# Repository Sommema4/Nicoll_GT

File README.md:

# Nicoll_GT
Gerdien tube documentation

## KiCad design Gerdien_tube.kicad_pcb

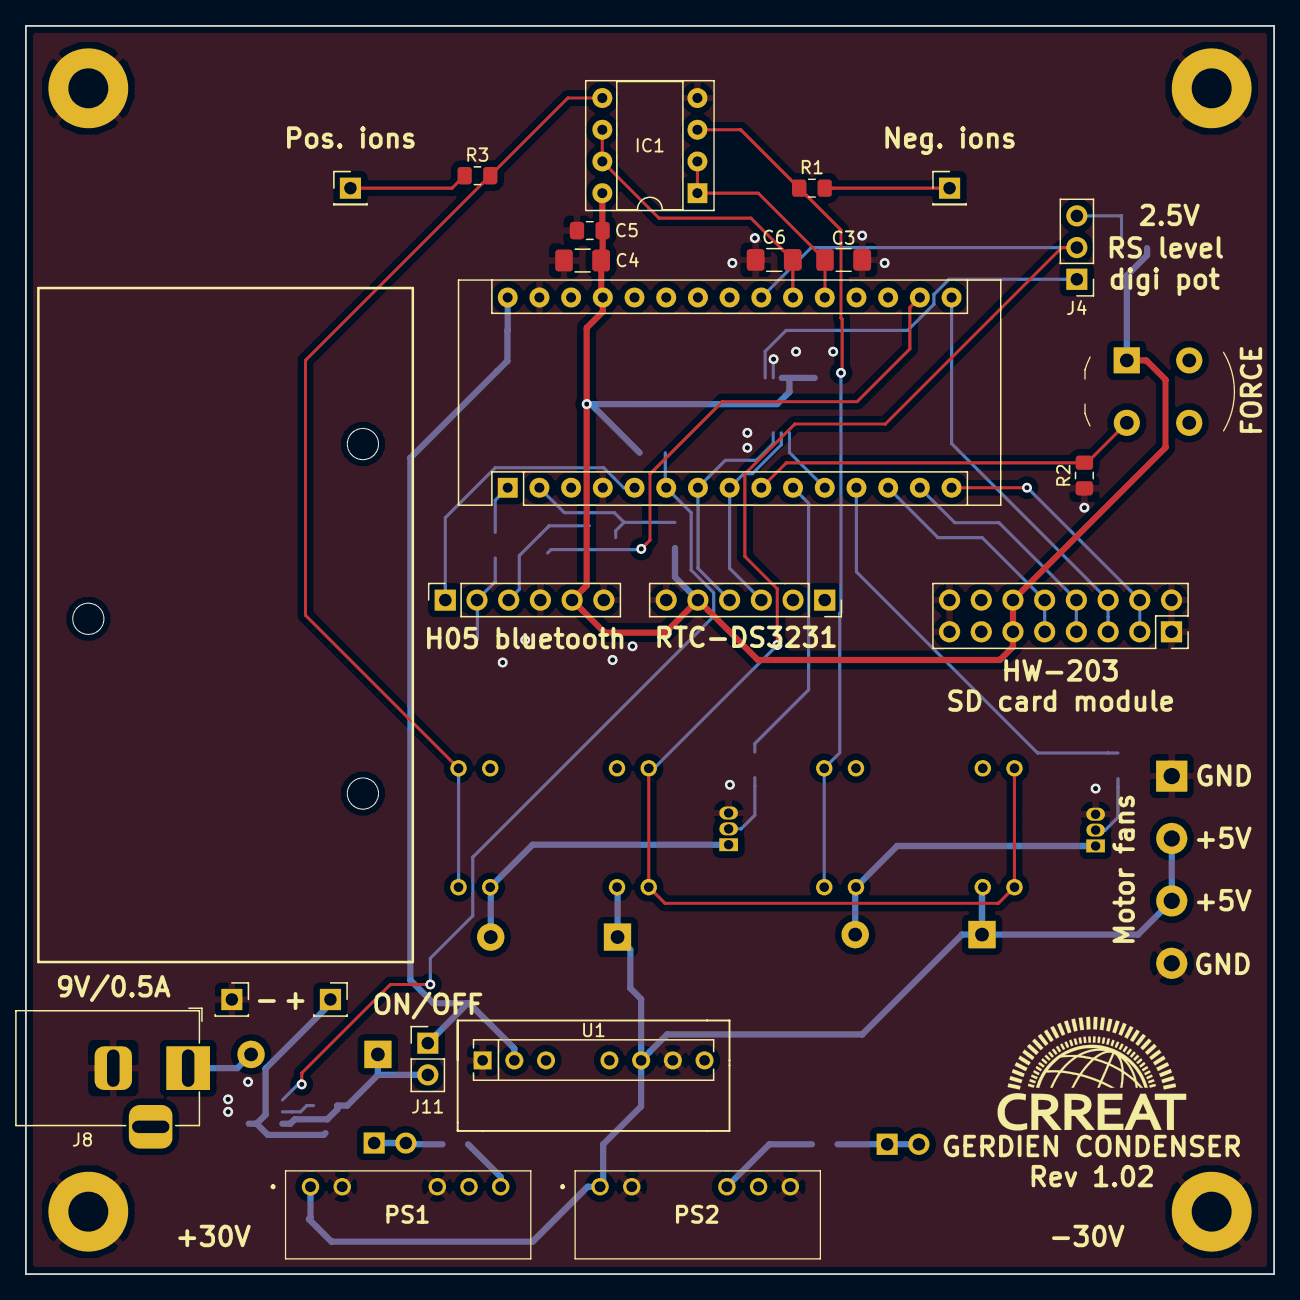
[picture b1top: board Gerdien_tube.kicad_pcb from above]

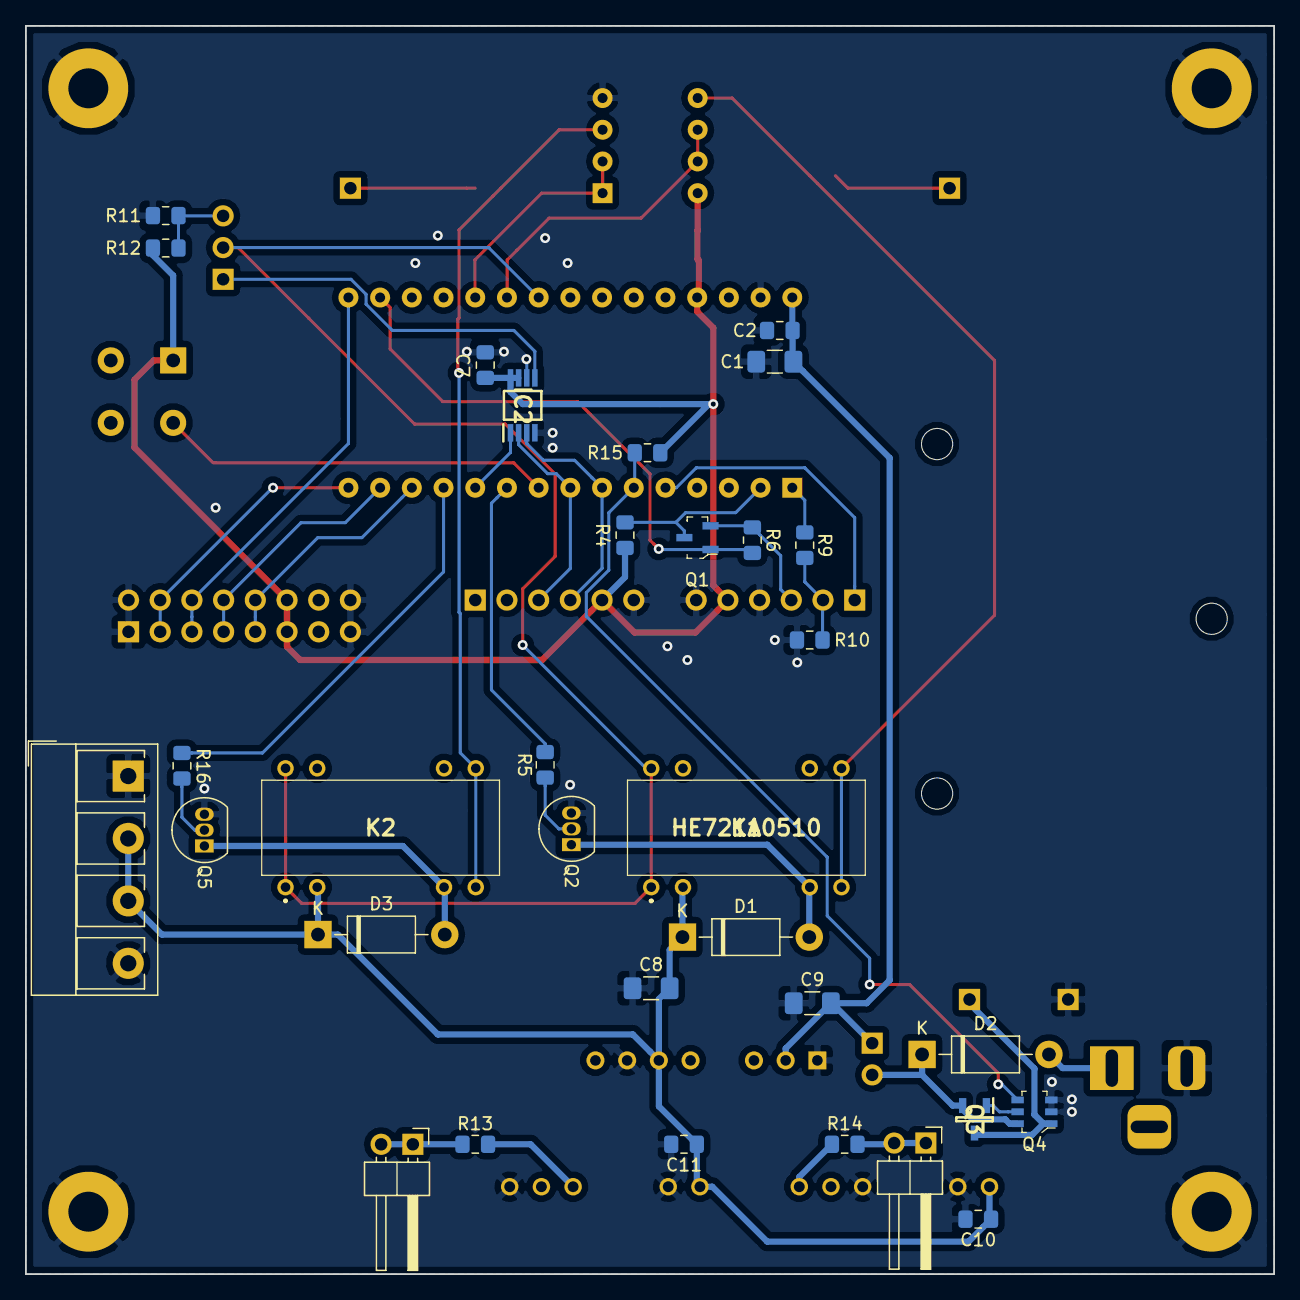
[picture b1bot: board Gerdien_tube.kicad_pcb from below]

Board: 2 copper layers, 100.0 x 100.0 mm, 62 parts (32 on the bottom side), 42 nets.

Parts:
A1: Arduino_Nano_v3.x; Arduino_Nano
C1, C3, C4, C6, C8: 10uF; C_1206_3216Metric_Pad1.42x1.75mm_HandSolder
C2, C7, C10, C11: 1uF; C_0805_2012Metric_Pad1.15x1.40mm_HandSolder
C5: 0.1uF; C_0805_2012Metric_Pad1.15x1.40mm_HandSolder
C9: 22uF; C_1206_3216Metric_Pad1.42x1.75mm_HandSolder
D1, D3: 1N4007; D_DO-41_SOD81_P10.16mm_Horizontal
D2: 1N5819; D_DO-41_SOD81_P10.16mm_Horizontal
IC1: LMC6042IM_NOPB; DIP-8_W7.62mm_Socket
IC2: CAT5140ZI-00-GT3; SOP65P490X110-8N
J1: Conn_02x08_Odd_Even; PinSocket_2x08_P2.54mm_Vertical
J2, J3: Conn_01x06_Female; PinSocket_1x06_P2.54mm_Vertical
J4: Conn_01x03_Male; PinHeader_1x03_P2.54mm_Vertical
J5: Screw_Terminal_01x04; TerminalBlock_RND_205-00278_1x04_P5.00mm_Vertical
J6, J7: Conn_01x01_Female; PinSocket_1x01_P2.54mm_Vertical
J8: Barrel_Jack; BarrelJack_Horizontal
J9, J10: Conn_01x02_Male; PinHeader_1x02_P2.54mm_Horizontal
J11: Conn_01x02_Male; PinHeader_1x02_P2.54mm_Vertical
K1, K2: HE721A0510
MH1, MH2, MH3, MH4: MountingHole_Pad; MountingHole_3.2mm_M3_Pad
MH5, MH6, MH7: MountingHole; MountingHole_2.5mm
PS1, PS2: RH-1215D; RP1212D
Q1: BSS138; SOT-23-3
Q2, Q5: BC547; TO-92_Inline
Q3: FDN306P; SOT95P237X112-3N
Q4: LTC4412ES6_TRMPBF; SOT-23-6
R1, R3: 1M; R_0805_2012Metric_Pad1.15x1.40mm_HandSolder
R2, R4, R6, R13, R14: 10k; R_0805_2012Metric_Pad1.15x1.40mm_HandSolder
R5, R9, R16: 1k; R_0805_2012Metric_Pad1.15x1.40mm_HandSolder
R10: 2k; R_0805_2012Metric_Pad1.15x1.40mm_HandSolder
R11, R12: 5k; R_0805_2012Metric_Pad1.15x1.40mm_HandSolder
R15: 470k; R_0805_2012Metric_Pad1.15x1.40mm_HandSolder
S1: GPTS203211B; PushButton_Round_D12mm_THT_KS-01Q-01
TP1, TP2: TestPoint; PinHeader_1x01_P2.54mm_Vertical
U1: TEC_3-0910; TEC3_0911

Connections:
+3V3: A1.17, Q1.1, R6.2
+5V: A1.27, C4.1, C5.1, C7.2, IC1.8, IC2.7, IC2.8, J1.11, J1.12, J2.5, J3.5, R4.2, R12.1, R15.1, S1.1
+5VP: C8.1, C10.1, C11.1, D1.1, D3.1, J5.2, J5.3, K1.2, K2.2, PS1.1, PS2.1, U1.6
+30V: J9.1, J9.2, R14.2
+BATT: J6.1, Q3.3, Q4.1
+VDC: A1.30, C1.1, C2.1, C9.1, J11.1, U1.2
-30V: J10.1, J10.2, R13.1
BUTTON: A1.9, R2.2, S1.2
CHANNEL_A: A1.20, C3.2, IC1.1, IC1.2
CHANNEL_B: A1.21, C6.2, IC1.6, IC1.7
CHARGE_1: IC1.5, K1.7, K1.8, R3.2
CHARGE_2: IC1.3, K2.7, K2.8, R1.1
CHARGE_LEVEL: A1.22, J4.2, K1.1, K1.14, K2.1, K2.14
CS: A1.13, J1.9, J1.10
DIG_POT: IC2.5, J4.1
GND: A1.4, A1.29, C1.2, C2.2, C3.1, C4.2, C5.2, C6.1, C7.1, C8.2, C9.2, C10.2, C11.2, IC1.4, IC2.4, IC2.6, J1.1, J1.2, J1.15, J1.16, J2.6, J3.4, J3.6, J5.1, J5.4, J7.1, J8.2, MH1.1, MH2.1, MH3.1, MH4.1, PS1.2, PS1.5, PS2.2, PS2.7, Q2.3, Q4.2, Q4.3, Q5.3, R2.1, R10.1, R11.2, U1.1, U1.7
H05_RX: A1.1, R9.2
H05_STATUS: A1.5, J3.1
H05_TX: A1.2, Q1.3, R4.1
MISO: A1.15, J1.3, J1.4
MOSI: A1.14, J1.7, J1.8
unnamed: D1.2, K1.6, Q2.1
unnamed: D2.1, J11.2, Q3.2, Q4.6
unnamed: D2.2, J8.1
unnamed: D3.2, K2.6, Q5.1
unnamed: J3.2, R9.1, R10.2
unnamed: J3.3, Q1.2, R6.1
unnamed: J4.3, R11.1, R12.2
unnamed: PS1.7, R14.1
unnamed: PS2.5, R13.2
unnamed: Q2.2, R5.1
unnamed: Q3.1, Q4.5
unnamed: Q5.2, R16.1
unnamed: R1.2, TP1.1
unnamed: R3.1, TP2.1
PWR_STATUS: A1.6, Q4.4, R15.2
RESET_1: A1.10, R5.2
RESET_2: A1.12, R16.2
SCK: A1.16, J1.5, J1.6
SCL: A1.8, IC2.2, J2.3
SDA: A1.7, IC2.3, J2.4
WP: A1.11, IC2.1

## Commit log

2020-08-20 Create a
2020-08-24 Create as
2020-11-12 Create a
    a
2020-11-12 Add files via upload
    balloon firmware
